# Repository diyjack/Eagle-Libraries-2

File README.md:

## Added by Phil Crump

* Element14 LTC Library

## Original Source as of 27th August 2012

Eagle Libraries and Boards for AVA HAB Project

Author : Anthony Stirk http://ava.upuaut.net

ava.lbr Contains :

* NTX2 Horizontal and Vertical Mounting
* uBLOX NEO-6 GPS
* uBLOX MAX-6 GPS
* Sarantel SL1202 Passive Antenna
* ADF7012 
* DS18B20 TO92
* DS18B20 SOIC
* Antenova GPS Module ( Part M10382 )
* ATMega 328P-AU
* JTI Chipscale Antenna
* LM2939 Regulator
* MOSFET (SOT223)
* Panasonic ELLVGG Inductor

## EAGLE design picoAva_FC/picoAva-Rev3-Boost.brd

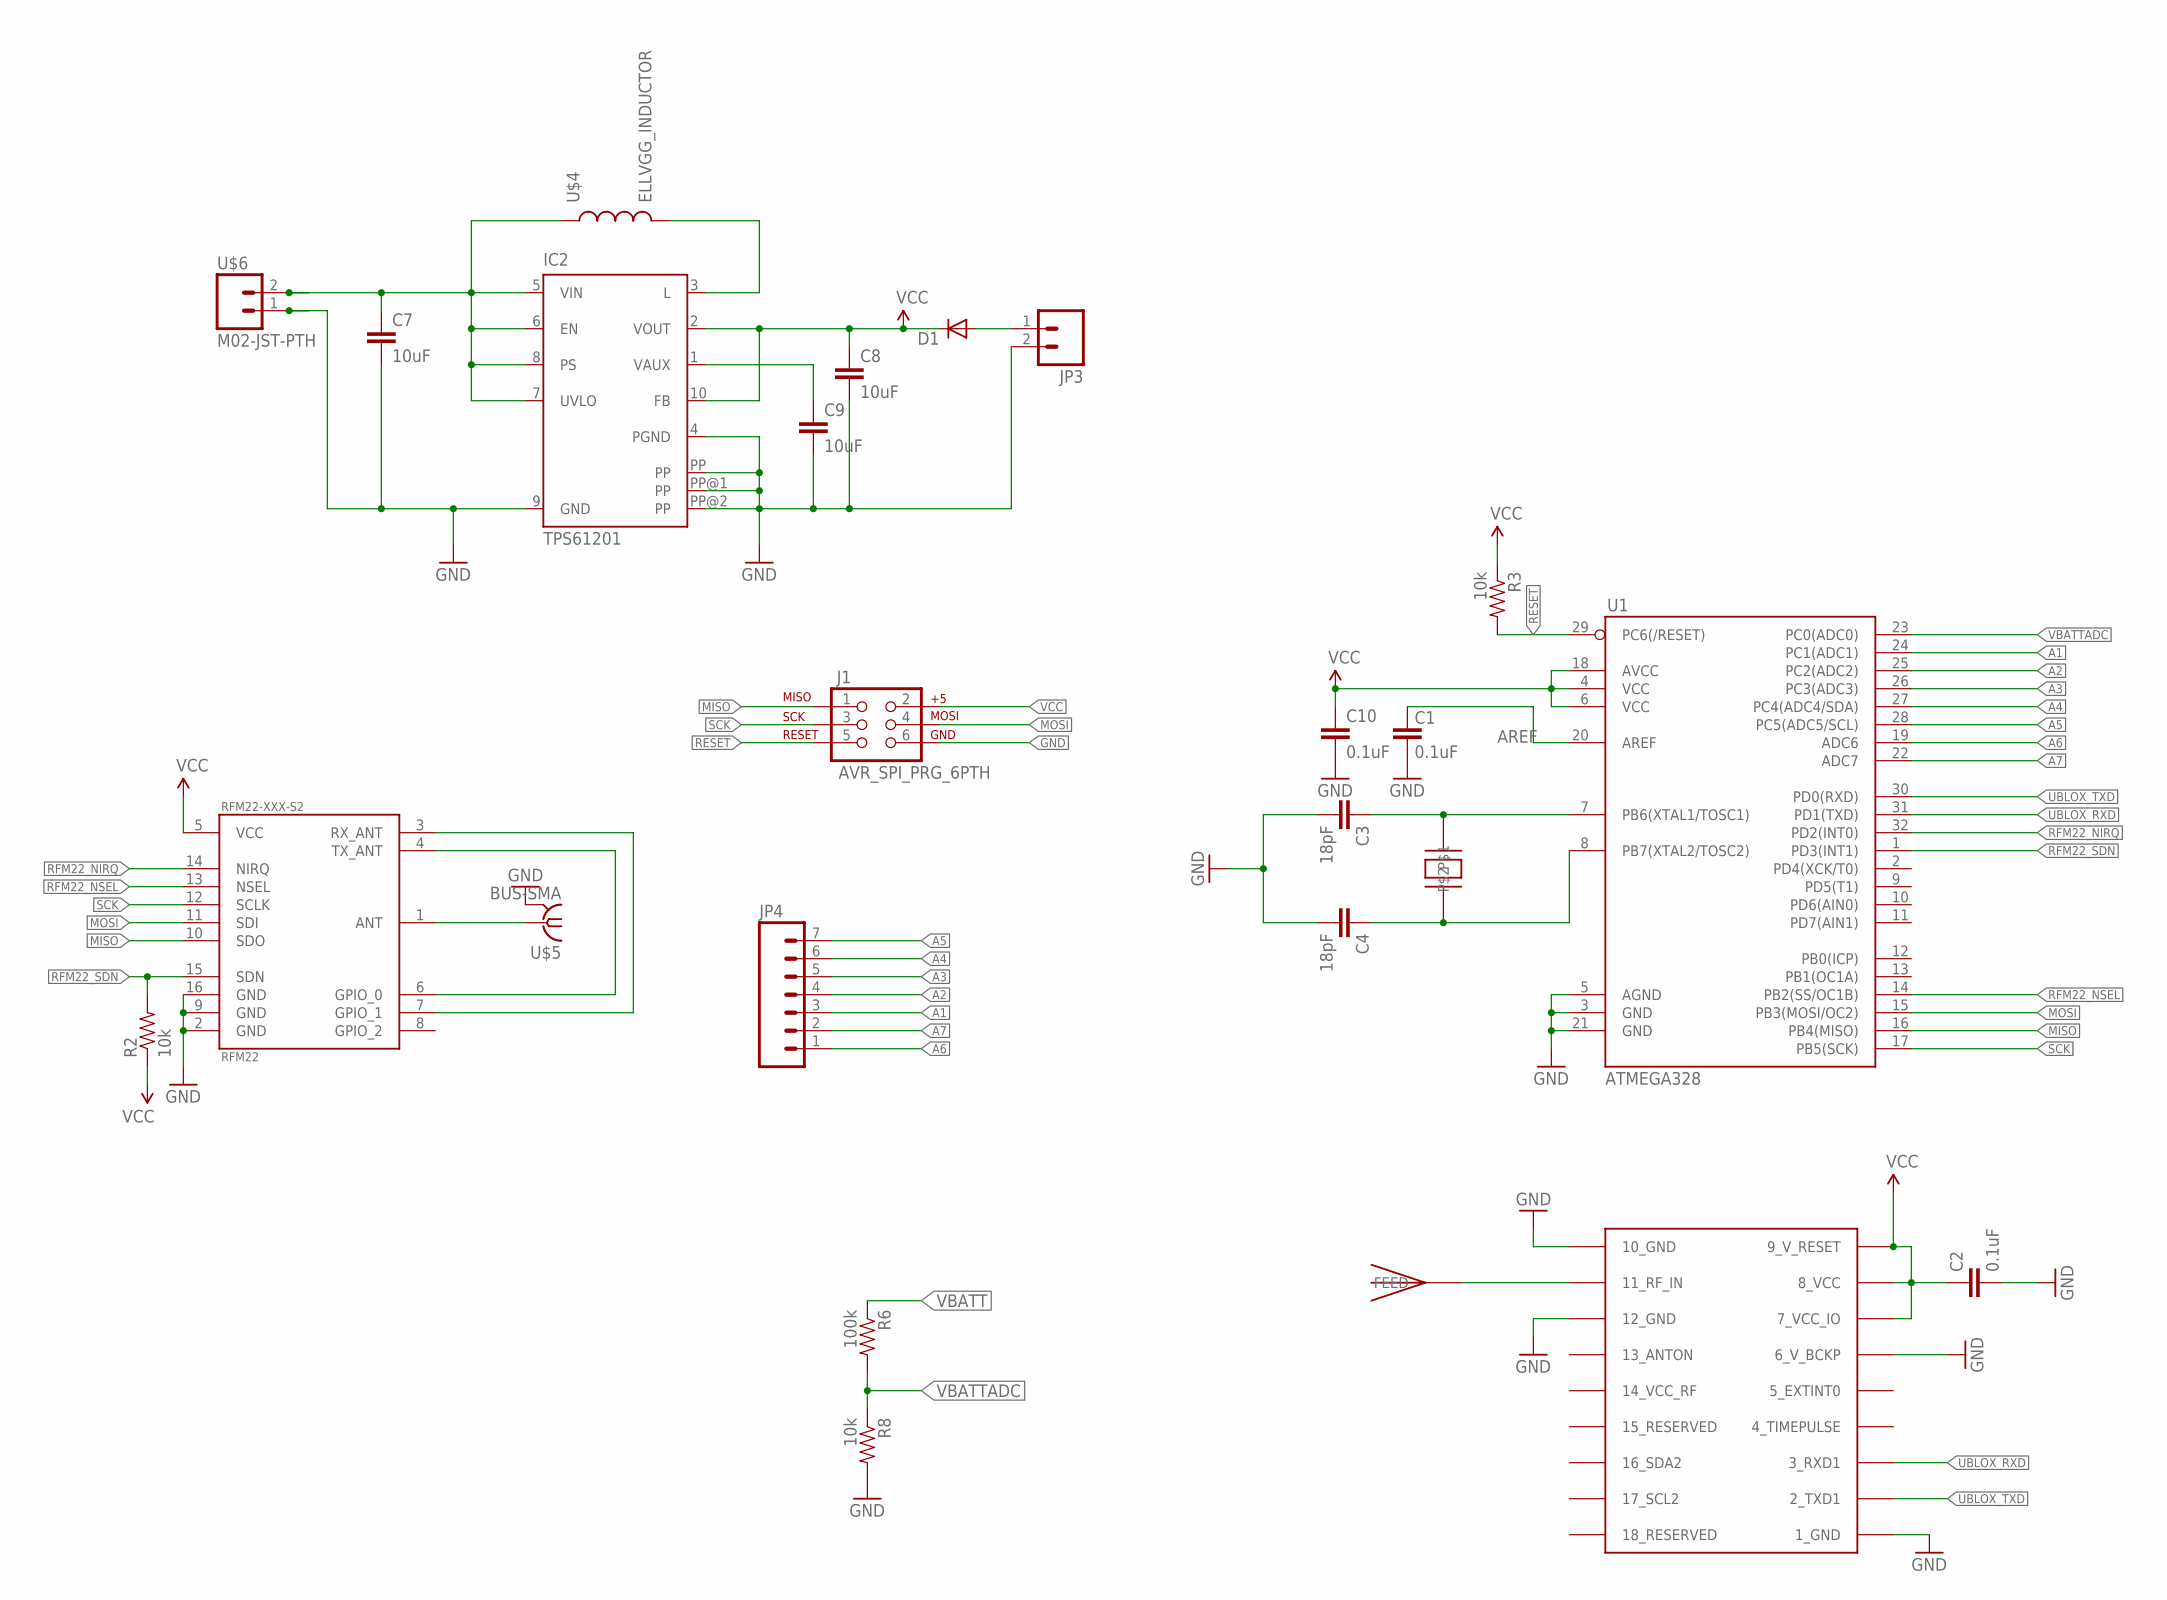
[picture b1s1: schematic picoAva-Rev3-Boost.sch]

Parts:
C1, C2, C10: 0.1uF; 0402-CAP
C3, C4: 18pF; 0402-CAP
C7, C8, C9: 10uF; 1206
D1: DIODESMA; SMA-DIODE
IC2: TPS61201; S-PDSO-N10
J1: AVR_SPI_PRG_6PTH; 2X3
JP3: M02PTH; 1X02
JP4: M07; 1X07
R2, R3, R8: 10k; 0402-RES
R6: 100k; 0402-RES
RFM22-XXX-S2: RFM22; RFM22-XXX-S2
U1: ATMEGA328; TQFP32-08
U$1: UBLOX_MAX-6
U$2: ABRACON_ABM3_CRYSTAL
U$3: JTI_ANTENNA-1575AT43A40
U$4: ELLVGG_INDUCTOR
U$5: BUS-SMA
U$6: M02-JST-PTH

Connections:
A1: JP4.3, U1.24 (PC1(ADC1))
A2: JP4.4, U1.25 (PC2(ADC2))
A3: JP4.5, U1.26 (PC3(ADC3))
A4: JP4.6, U1.27 (PC4(ADC4/SDA))
A5: JP4.7, U1.28 (PC5(ADC5/SCL))
A6: JP4.1, U1.19 (ADC6)
A7: JP4.2, U1.22 (ADC7)
AREF: C1.2, U1.20 (AREF)
GND: C1.1, C2.2, C3.2, C4.2, C7.2, C8.2, C9.2, C10.2, IC2.4 (PGND), IC2.9 (GND), IC2.PP, IC2.PP@1 (PP), IC2.PP@2 (PP), J1.6, JP3.2, R8.2, RFM22-XXX-S2.2 (GND), RFM22-XXX-S2.9 (GND), RFM22-XXX-S2.16 (GND), U1.3 (GND), U1.5 (AGND), U1.21 (GND), U$1.1_GND, U$1.6_V_BCKP, U$1.10_GND, U$1.12_GND, U$5.2 (GND), U$5.3 (GND), U$5.4 (GND), U$5.5 (GND), U$6.1
MISO: J1.1, RFM22-XXX-S2.10 (SDO), U1.16 (PB4(MISO))
MOSI: J1.4, RFM22-XXX-S2.11 (SDI), U1.15 (PB3(MOSI/OC2))
unnamed: D1.A, JP3.1
unnamed: RFM22-XXX-S2.1 (ANT), U$5.1
unnamed: U$1.11_RF_IN, U$3.FEED
unnamed: RFM22-XXX-S2.3 (RX_ANT), RFM22-XXX-S2.7 (GPIO_1)
unnamed: RFM22-XXX-S2.4 (TX_ANT), RFM22-XXX-S2.6 (GPIO_0)
unnamed: IC2.3 (L), U$4.P$2 (2)
unnamed: C3.1, U1.7 (PB6(XTAL1/TOSC1)), U$2.P$2
unnamed: C4.1, U1.8 (PB7(XTAL2/TOSC2)), U$2.P$1
unnamed: C9.1, IC2.1 (VAUX)
RESET: J1.5, R3.2, U1.29 (PC6(/RESET))
RFM22_NIRQ: RFM22-XXX-S2.14 (NIRQ), U1.32 (PD2(INT0))
RFM22_NSEL: RFM22-XXX-S2.13 (NSEL), U1.14 (PB2(SS/OC1B))
RFM22_SDN: R2.2, RFM22-XXX-S2.15 (SDN), U1.1 (PD3(INT1))
SCK: J1.3, RFM22-XXX-S2.12 (SCLK), U1.17 (PB5(SCK))
UBLOX_RXD: U1.31 (PD1(TXD)), U$1.3_RXD1
UBLOX_TXD: U1.30 (PD0(RXD)), U$1.2_TXD1
VBATT: C7.1, IC2.5 (VIN), IC2.6 (EN), IC2.7 (UVLO), IC2.8 (PS), R6.1, U$4.P$1 (1), U$6.2
VBATTADC: R6.2, R8.1, U1.23 (PC0(ADC0))
VCC: C2.1, C8.1, C10.1, D1.C, IC2.2 (VOUT), IC2.10 (FB), J1.2, R2.1, R3.1, RFM22-XXX-S2.5 (VCC), U1.4 (VCC), U1.6 (VCC), U1.18 (AVCC), U$1.7_VCC_IO, U$1.8_VCC, U$1.9_V_RESET

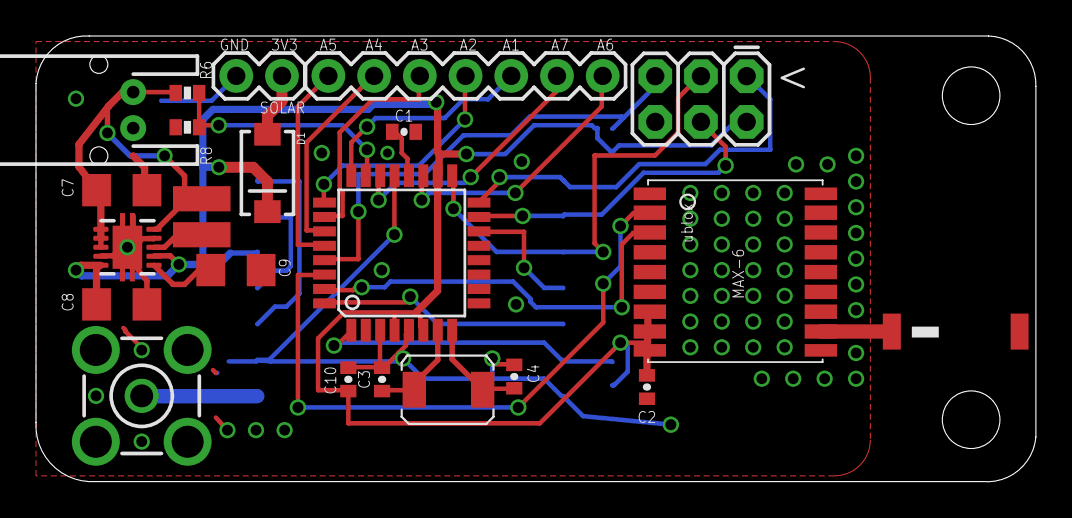
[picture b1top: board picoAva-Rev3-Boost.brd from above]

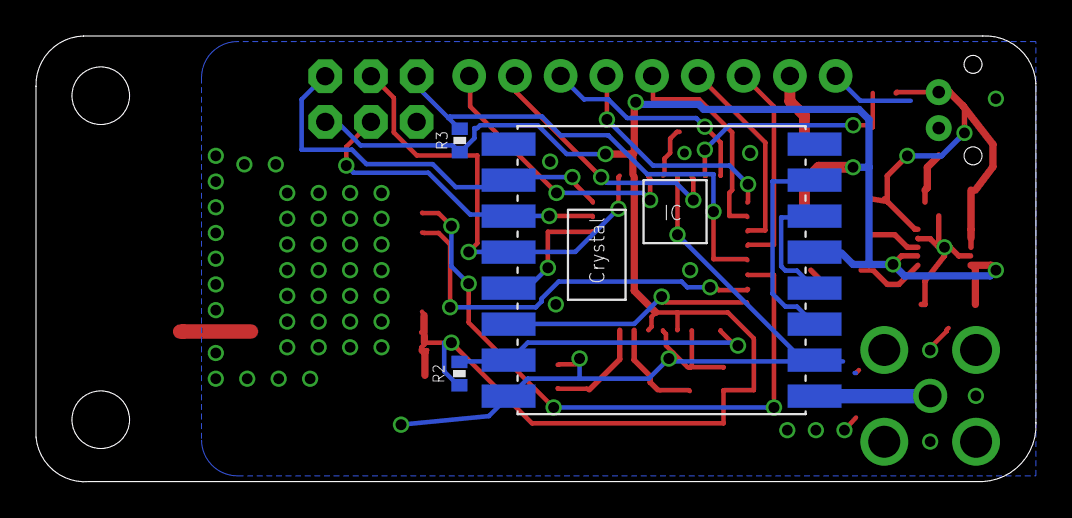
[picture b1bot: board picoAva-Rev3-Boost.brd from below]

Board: 2 copper layers, 55.5 x 24.8 mm, 25 parts (3 on the bottom side), 30 nets.

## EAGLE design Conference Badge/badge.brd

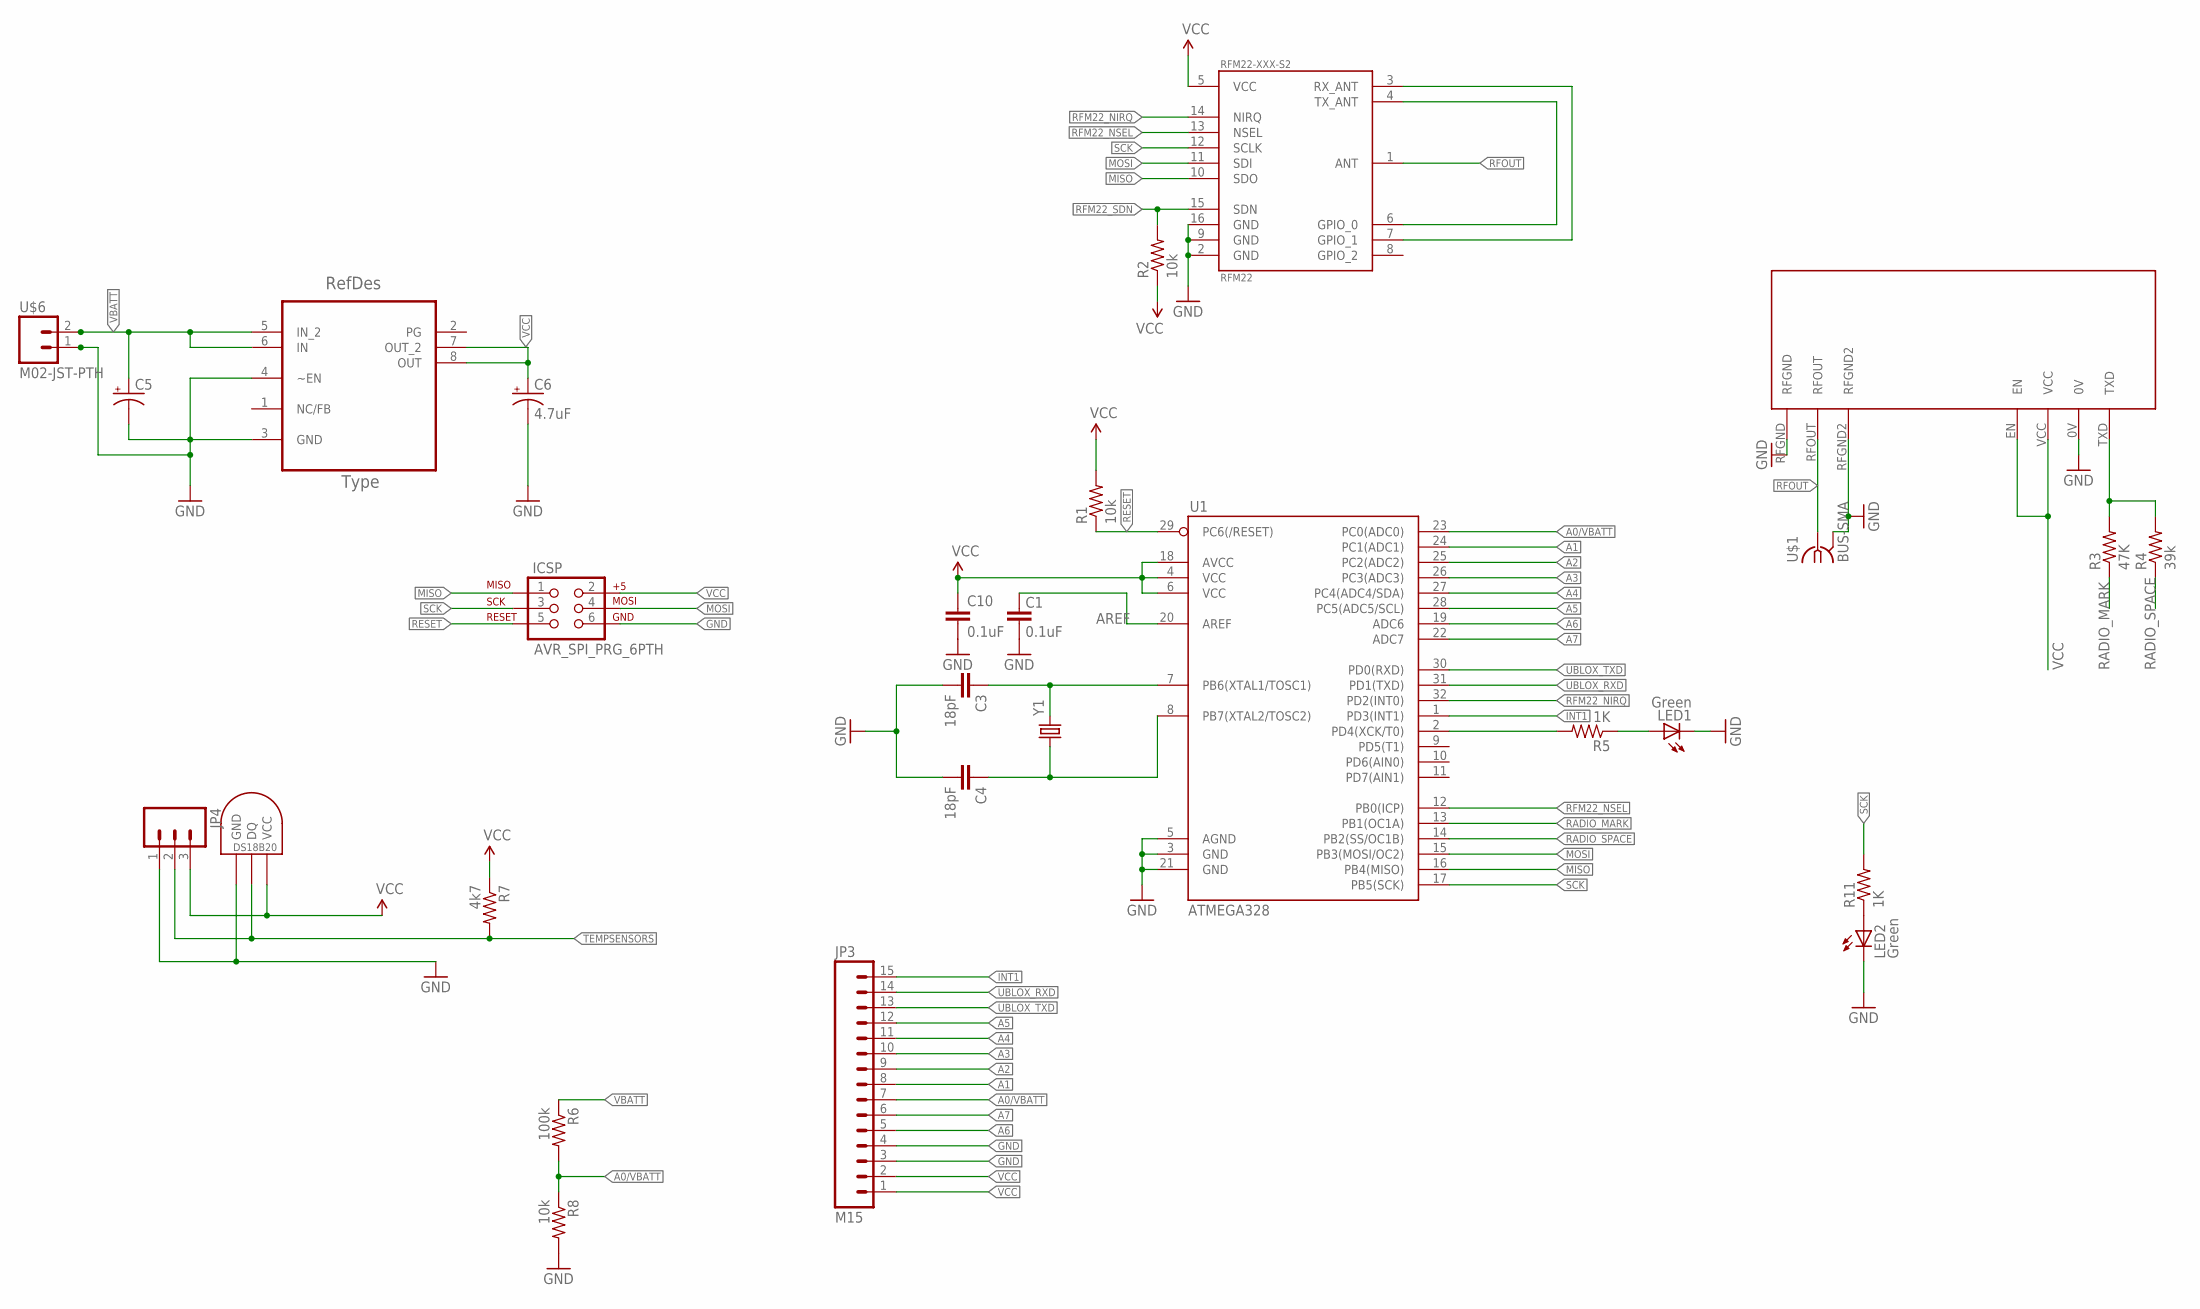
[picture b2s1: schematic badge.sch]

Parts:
C1, C10: 0.1uF; 0603-CAP
C3, C4: 18pF; 0603-CAP
C5: CAP_POL1206-KIT; EIA3216-KIT
C6: 4.7uF; EIA3216-KIT
ICSP: AVR_SPI_PRG_6PTH; 2X3
JP3: M15; 1X15
JP4: M03PTH; 1X03
LED1, LED2: Green; LED-0603
NTX2TEMP: DS1821; DS18B20_SOIC
R1, R2, R8: 10k; 0603-RES
R3: 47K; 0603-RES
R4: 39k; 0603-RES
R5, R11: 1K; 0603-RES
R6: 100k; 0603-RES
R7: 4k7; 0603-RES
RFM22-XXX-S2: RFM22; RFM22-XXX-S2
U1: ATMEGA328; TQFP32-08
U2: TPS76633D; SOIC127P600X175-8N
U$1: BUS-SMA
U$4: NTX2
U$6: M02-JST-PTH
Y1: CRYSTALSMD; HC49UP

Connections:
A0/VBATT: JP3.7, R6.2, R8.1, U1.23 (PC0(ADC0))
A1: JP3.8, U1.24 (PC1(ADC1))
A2: JP3.9, U1.25 (PC2(ADC2))
A3: JP3.10, U1.26 (PC3(ADC3))
A4: JP3.11, U1.27 (PC4(ADC4/SDA))
A5: JP3.12, U1.28 (PC5(ADC5/SCL))
A6: JP3.5, U1.19 (ADC6)
A7: JP3.6, U1.22 (ADC7)
AREF: C1.2, U1.20 (AREF)
GND: C1.1, C3.2, C4.2, C5.C (-), C6.C (-), C10.2, ICSP.6, JP3.3, JP3.4, JP4.1, LED1.C, LED2.C, NTX2TEMP.GND, R8.2, RFM22-XXX-S2.2 (GND), RFM22-XXX-S2.9 (GND), RFM22-XXX-S2.16 (GND), U1.3 (GND), U1.5 (AGND), U1.21 (GND), U2.3 (GND), U2.4 (~EN), U$1.2 (GND), U$1.3 (GND), U$1.4 (GND), U$1.5 (GND), U$4.0V, U$4.RFGND, U$4.RFGND2, U$6.1
INT1: JP3.15, U1.1 (PD3(INT1))
MISO: ICSP.1, RFM22-XXX-S2.10 (SDO), U1.16 (PB4(MISO))
MOSI: ICSP.4, RFM22-XXX-S2.11 (SDI), U1.15 (PB3(MOSI/OC2))
unnamed: R5.2, U1.2 (PD4(XCK/T0))
unnamed: R3.2, R4.2, U$4.TXD
unnamed: LED1.A, R5.1
unnamed: RFM22-XXX-S2.3 (RX_ANT), RFM22-XXX-S2.7 (GPIO_1)
unnamed: RFM22-XXX-S2.4 (TX_ANT), RFM22-XXX-S2.6 (GPIO_0)
unnamed: LED2.A, R11.1
unnamed: C3.1, U1.7 (PB6(XTAL1/TOSC1)), Y1.2
unnamed: C4.1, U1.8 (PB7(XTAL2/TOSC2)), Y1.1
RADIO_MARK: R3.1, U1.13 (PB1(OC1A))
RADIO_SPACE: R4.1, U1.14 (PB2(SS/OC1B))
RESET: ICSP.5, R1.1, U1.29 (PC6(/RESET))
RFM22_NIRQ: RFM22-XXX-S2.14 (NIRQ), U1.32 (PD2(INT0))
RFM22_NSEL: RFM22-XXX-S2.13 (NSEL), U1.12 (PB0(ICP))
RFM22_SDN: R2.2, RFM22-XXX-S2.15 (SDN)
RFOUT: RFM22-XXX-S2.1 (ANT), U$1.1, U$4.RFOUT
SCK: ICSP.3, R11.2, RFM22-XXX-S2.12 (SCLK), U1.17 (PB5(SCK))
TEMPSENSORS: JP4.2, NTX2TEMP.DQ, R7.2
UBLOX_RXD: JP3.14, U1.31 (PD1(TXD))
UBLOX_TXD: JP3.13, U1.30 (PD0(RXD))
VBATT: C5.A (+), R6.1, U2.5 (IN_2), U2.6 (IN), U$6.2
VCC: C6.A (+), C10.1, ICSP.2, JP3.1, JP3.2, JP4.3, NTX2TEMP.VCC, R1.2, R2.1, R7.1, RFM22-XXX-S2.5 (VCC), U1.4 (VCC), U1.6 (VCC), U1.18 (AVCC), U2.7 (OUT_2), U2.8 (OUT), U$4.EN, U$4.VCC

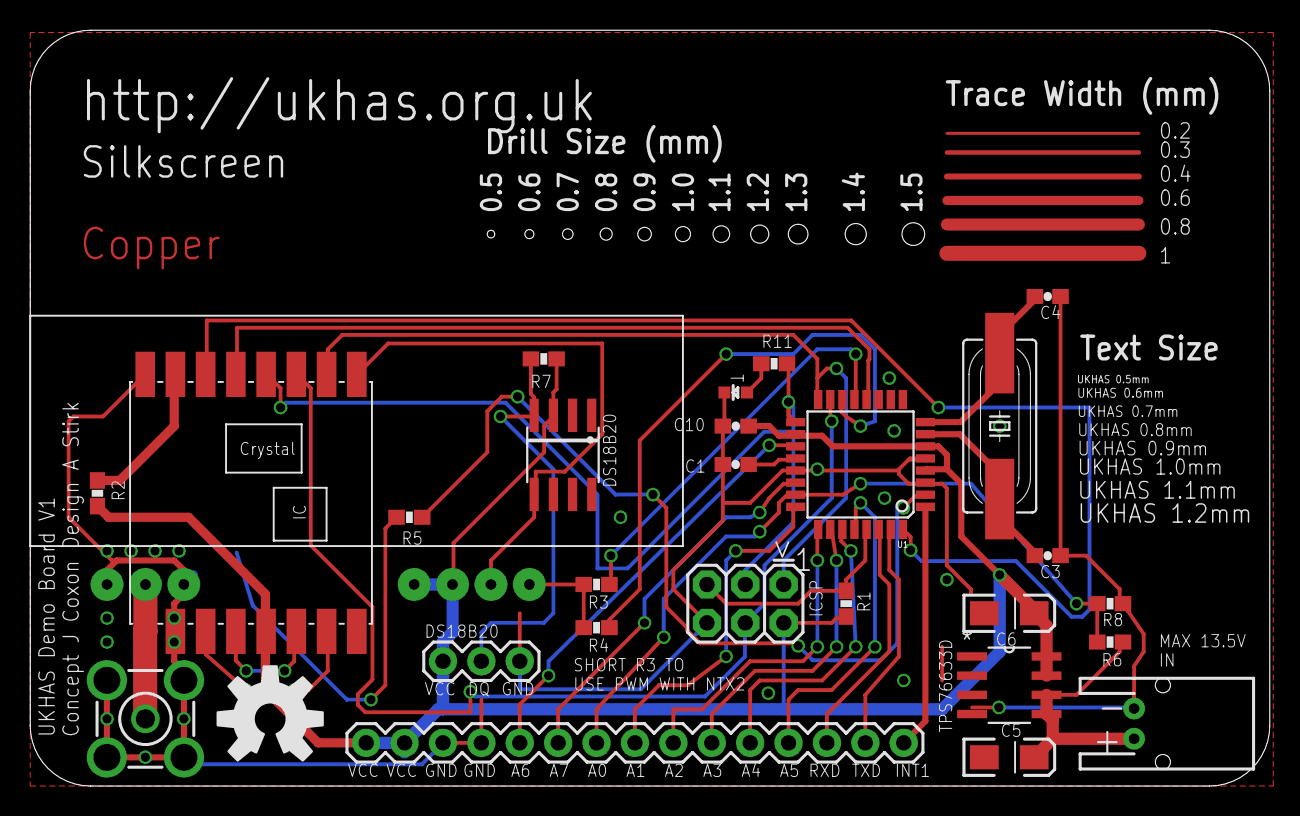
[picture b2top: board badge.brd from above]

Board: 2 copper layers, 82.0 x 50.0 mm, 29 parts (1 on the bottom side), 34 nets.

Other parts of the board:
U$2: OSHW-LOGO-L

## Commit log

2012-07-02 Commit of ignore file.
2012-07-02 Amended
2012-07-02 Another 1
2012-07-02 1233
2012-07-02 Added badge
2012-07-02 Correction
2012-07-02 Pew pew
2012-07-31 Removed older versions
2012-08-23 Update libraries
2012-08-27 Add Linear-Tech-3 lbr
2012-08-27 Supersede LTC library with Element14 zip.
2012-08-27 Updated README.
2012-08-27 Enabled markdown in README.
2012-08-27 Customised .gitignore
2012-08-27 Add Element14 Microchip library.
2012-08-27 Add Element14 Vishay library.
2012-08-27 Moved Upus schematics into folder.
2012-10-04 README: Bullet ava.lbr list
2012-10-05 Add Multicump element14 lbr
2013-01-01 Merge additions and changes.
    Merge with version kept in dropbox.
2013-01-02 Add latest Hackvana CAM script.
2013-01-12 Eagle-ify of Hackvana CAM script.
2013-01-12 Add Hackvana Design rules file (dru)
2013-06-05 Add Maxim Library.
2013-07-15 Add SCORCH lbr with MAX1947
2013-07-15 Add SPM6530 Inductor to SCORCH lbr.
2013-07-15 Add BALUN433, fix layers in other devices.
2013-07-15 Add 26MHz XTAL to SCORCH lbr.
